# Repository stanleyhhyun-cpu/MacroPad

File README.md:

# MacroPad Stanley Hyun
This project is called Study Pad because it will help students study! This will help students study using the Pomodoro Technique. The Pomodoro technique involves studying for 25 minutes and taking a 5-minute break in between. Each button on the hackpad will serve a different purpose. For example, the first button starts the 25-minute study timer, the second starts the 5-minute break timer, the third resets the timer, and the fourth kills the device by shutting it off. Each button will have an LED behind it. The device will have a speaker that sounds every time the 25 minute alarm goes off.

Screenshot of overall Hackpad - 
Screenshot of Schematic - 
Screenshot of PCB - 
Screenshot of BOM

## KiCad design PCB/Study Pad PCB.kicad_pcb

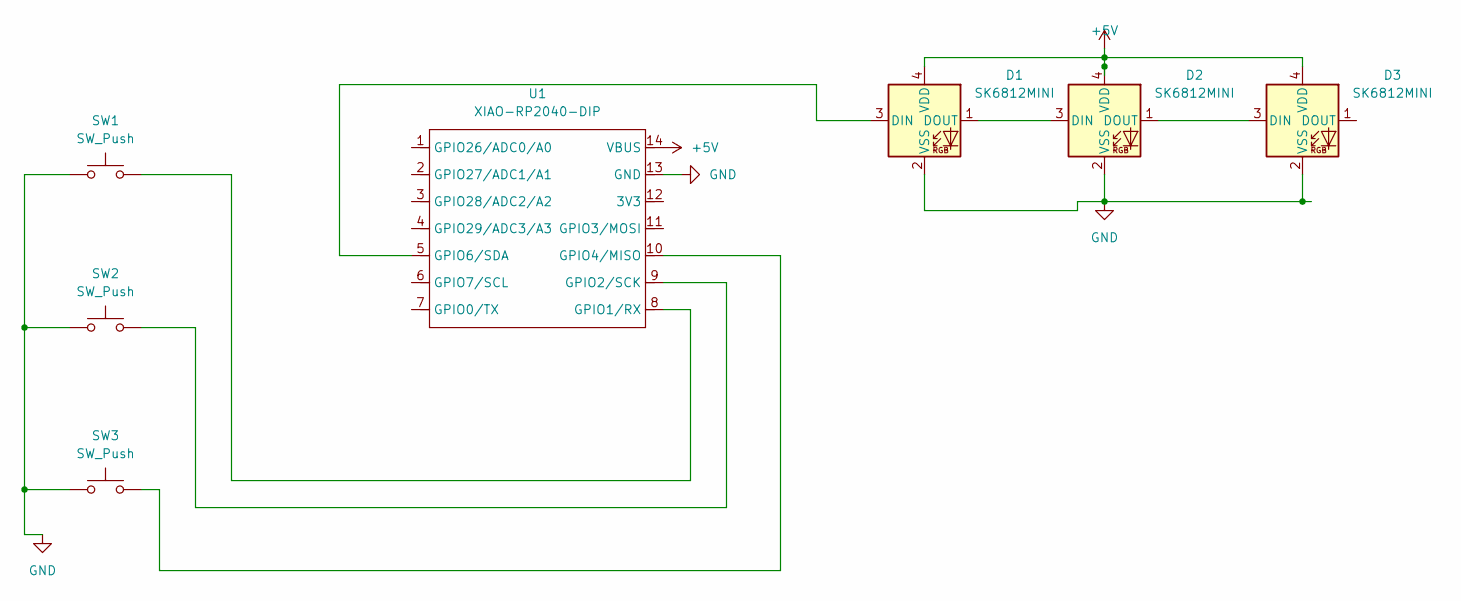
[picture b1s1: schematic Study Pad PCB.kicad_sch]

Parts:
D1, D2, D3: SK6812MINI; LED_SK6812MINI_PLCC4_3.5x3.5mm_P1.75mm
SW1, SW2, SW3: SW_Push; SW_Cherry_MX_1.00u_PCB
U1: XIAO-RP2040-DIP

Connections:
+5V: D1.4 (VDD), D2.4 (VDD), D3.4 (VDD), U1.14 (VBUS)
GND: D1.2 (VSS), D2.2 (VSS), D3.2 (VSS), SW1.1, SW2.1, SW3.1, U1.13 (GND)
unnamed: D1.3 (DIN), U1.5 (GPIO6/SDA)
unnamed: D1.1 (DOUT), D2.3 (DIN)
unnamed: D2.1 (DOUT), D3.3 (DIN)
unnamed: SW1.2, U1.8 (GPIO1/RX)
unnamed: SW2.2, U1.9 (GPIO2/SCK)
unnamed: SW3.2, U1.10 (GPIO4/MISO)

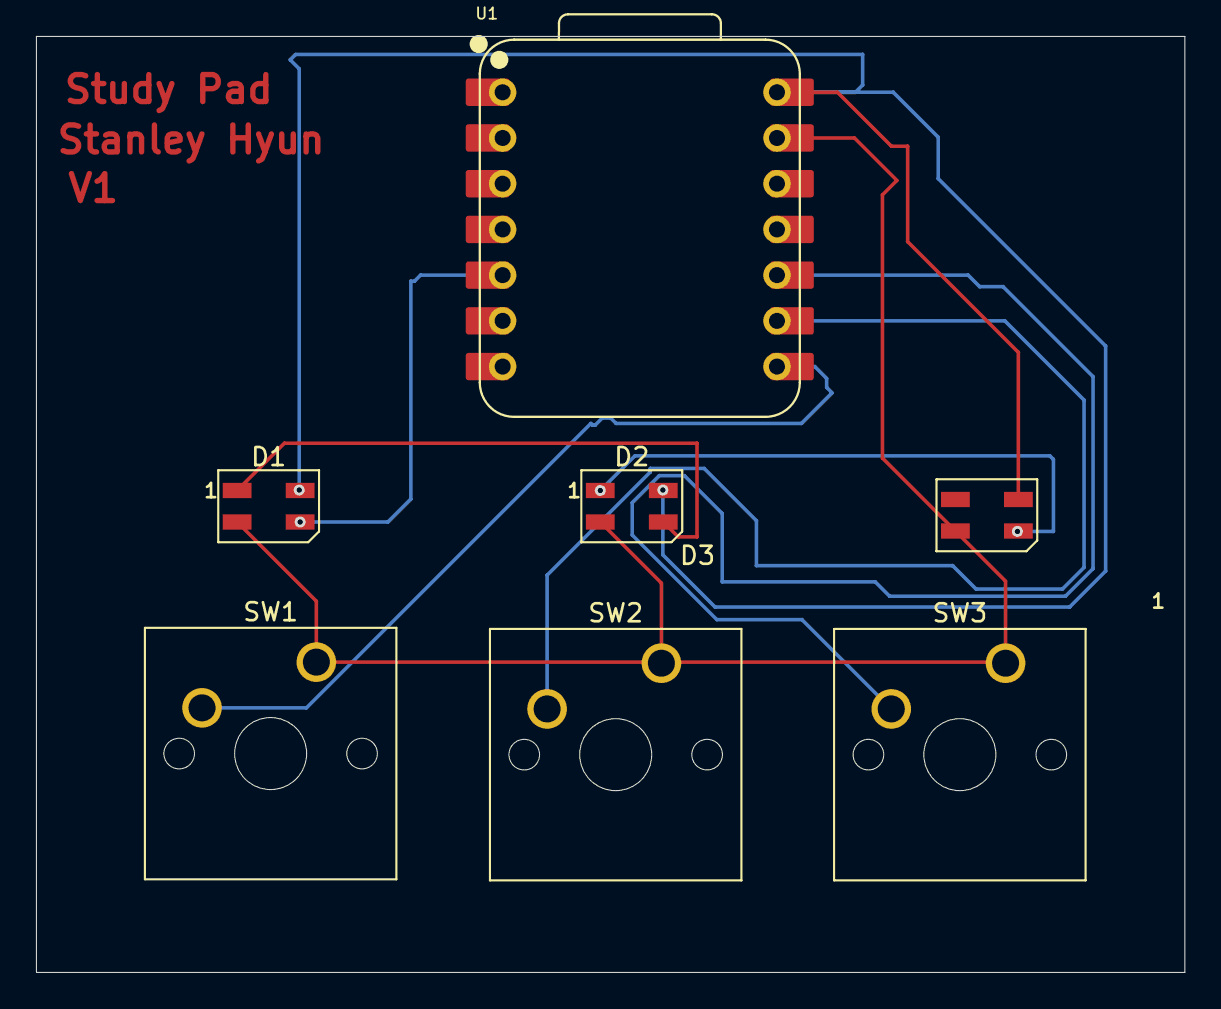
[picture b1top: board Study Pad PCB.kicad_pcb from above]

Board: 2 copper layers, 63.8 x 52.0 mm, 7 parts (0 on the bottom side), 8 nets.

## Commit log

2026-04-07 Create temp
